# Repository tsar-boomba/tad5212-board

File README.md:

# TAD5212 Breakout Board

A breadboard compatible breakout for [TI's TAD5212 DAC+amp IC](https://www.ti.com/product/TAD5212#design-development). If you wanna produce this, just zip the gerbers folder and get it manufactured. That's it.

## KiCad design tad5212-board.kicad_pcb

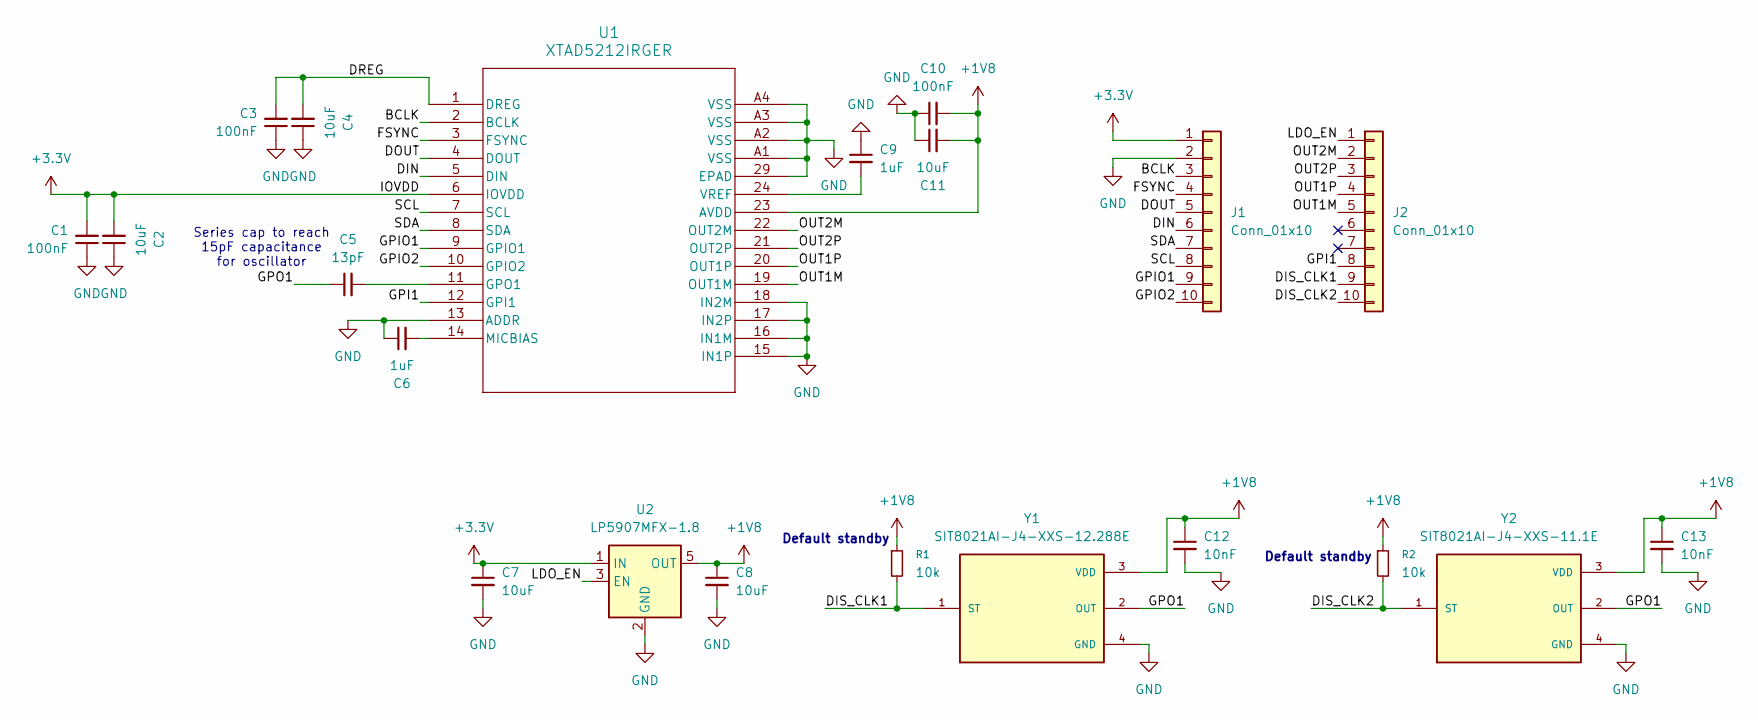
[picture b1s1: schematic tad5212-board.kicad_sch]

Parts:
C1, C3, C10: 100nF; C_0603_1608Metric
C2, C4, C7, C8, C11: 10uF; C_0805_2012Metric
C5: 13pF; C_0603_1608Metric
C6, C9: 1uF; C_0603_1608Metric
C12, C13: 10nF; C_0603_1608Metric
J1, J2: Conn_01x10; PinHeader_1x10_P2.54mm_Vertical; LCSC PN C5383117
R1, R2: 10k; R_0603_1608Metric
U1: XTAD5212IRGER; VQFN24_RGE_CORNERPADS_TEX; LCSC PN C45068920
U2: LP5907MFX-1.8; SOT-23-5
Y1: SIT8021AI-J4-XXS-12.288E; OSC_SIT8021AI-J4-XXS-24.000000E; PARTREV 1.32
Y2: SIT8021AI-J4-XXS-11.1E; OSC_SIT8021AI-J4-XXS-24.000000E; PARTREV 1.32

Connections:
+1V8: C8.1, C10.2, C11.2, C12.1, C13.1, R1.1, R2.1, U1.23 (AVDD), U2.5 (OUT), Y1.3 (VDD), Y2.3 (VDD)
+3.3V: C1.2, C2.2, C7.1, J1.1, U1.6 (IOVDD), U2.1 (IN)
/BCLK: J1.3, U1.2 (BCLK)
/DIN: J1.6, U1.5 (DIN)
/DIS_CLK1: J2.9, R1.2, Y1.1 (ST)
/DIS_CLK2: J2.10, R2.2, Y2.1 (ST)
/DOUT: J1.5, U1.4 (DOUT)
/DREG: C3.2, C4.2, U1.1 (DREG)
/FSYNC: J1.4, U1.3 (FSYNC)
/GPI1: J2.8, U1.12 (GPI1)
/GPIO1: J1.9, U1.9 (GPIO1)
/GPIO2: J1.10, U1.10 (GPIO2)
/GPO1: C5.1, Y1.2 (OUT), Y2.2 (OUT)
/LDO_EN: J2.1, U2.3 (EN)
/OUT1M: J2.5, U1.19 (OUT1M)
/OUT1P: J2.4, U1.20 (OUT1P)
/OUT2M: J2.2, U1.22 (OUT2M)
/OUT2P: J2.3, U1.21 (OUT2P)
/SCL: J1.8, U1.7 (SCL)
/SDA: J1.7, U1.8 (SDA)
GND: C1.1, C2.1, C3.1, C4.1, C6.1, C7.2, C8.2, C9.1, C10.1, C11.1, C12.2, C13.2, J1.2, U1.13 (ADDR), U1.15 (IN1P), U1.16 (IN1M), U1.17 (IN2P), U1.18 (IN2M), U1.29 (EPAD), U1.A1 (VSS), U1.A2 (VSS), U1.A3 (VSS), U1.A4 (VSS), U2.2 (GND), Y1.4 (GND), Y2.4 (GND)
unnamed: C5.2, U1.11 (GPO1)
unnamed: C6.2, U1.14 (MICBIAS)
unnamed: C9.2, U1.24 (VREF)

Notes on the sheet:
Series cap to reach 15pF capacitance for oscillator
Default standby

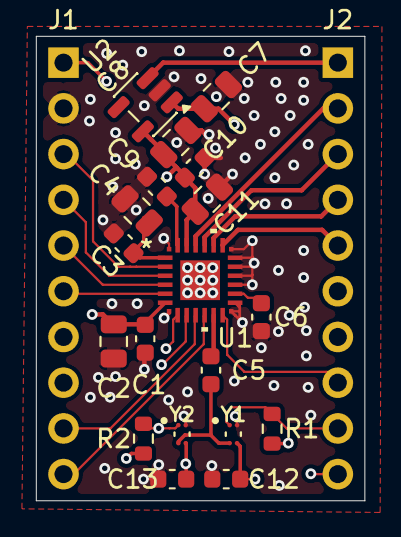
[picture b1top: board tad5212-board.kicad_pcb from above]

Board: 4 copper layers, 18.2 x 25.8 mm, 21 parts (0 on the bottom side), 24 nets.

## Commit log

2026-02-15 tad5212-board v0
2026-02-15 LICENSE
2026-02-15 add readme
2026-03-24 v2 with hive compat footprints and fix i2c
2026-03-24 commit all gerbers
2026-03-24 make 4-layer; add ldo
2026-03-30 add via stitching
2026-04-03 add oscillator
2026-04-03 space out fsync and bclk a lil bit
2026-04-06 redo annotations
